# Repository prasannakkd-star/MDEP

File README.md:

# MDEP - Modular Distributed Embedded Platform

## Overview

MDEP is a modular embedded electronics platform built around a central motherboard and interchangeable peripheral modules.

## Hardware Modules

- Mainboard (prasanna) - central platform

- Audio Hub - audio-related module

- Motor Driver Hub - motor-control interface

- Sensor Hub - sensor interface

## Tools

- KiCad - schematic capture and PCB design

- Git - local version control

- GitHub - planned remote repository

## Development Status

- [x] Initial schematics and PCB layouts committed locally

- [ ] Assemble and test hardware

## Goals

- Reusable modular hardware

- Clear interfaces between modules

- Easier prototyping, debugging, and future expansion

## Notes

Hardware features and validation status will be updated as development progresses.

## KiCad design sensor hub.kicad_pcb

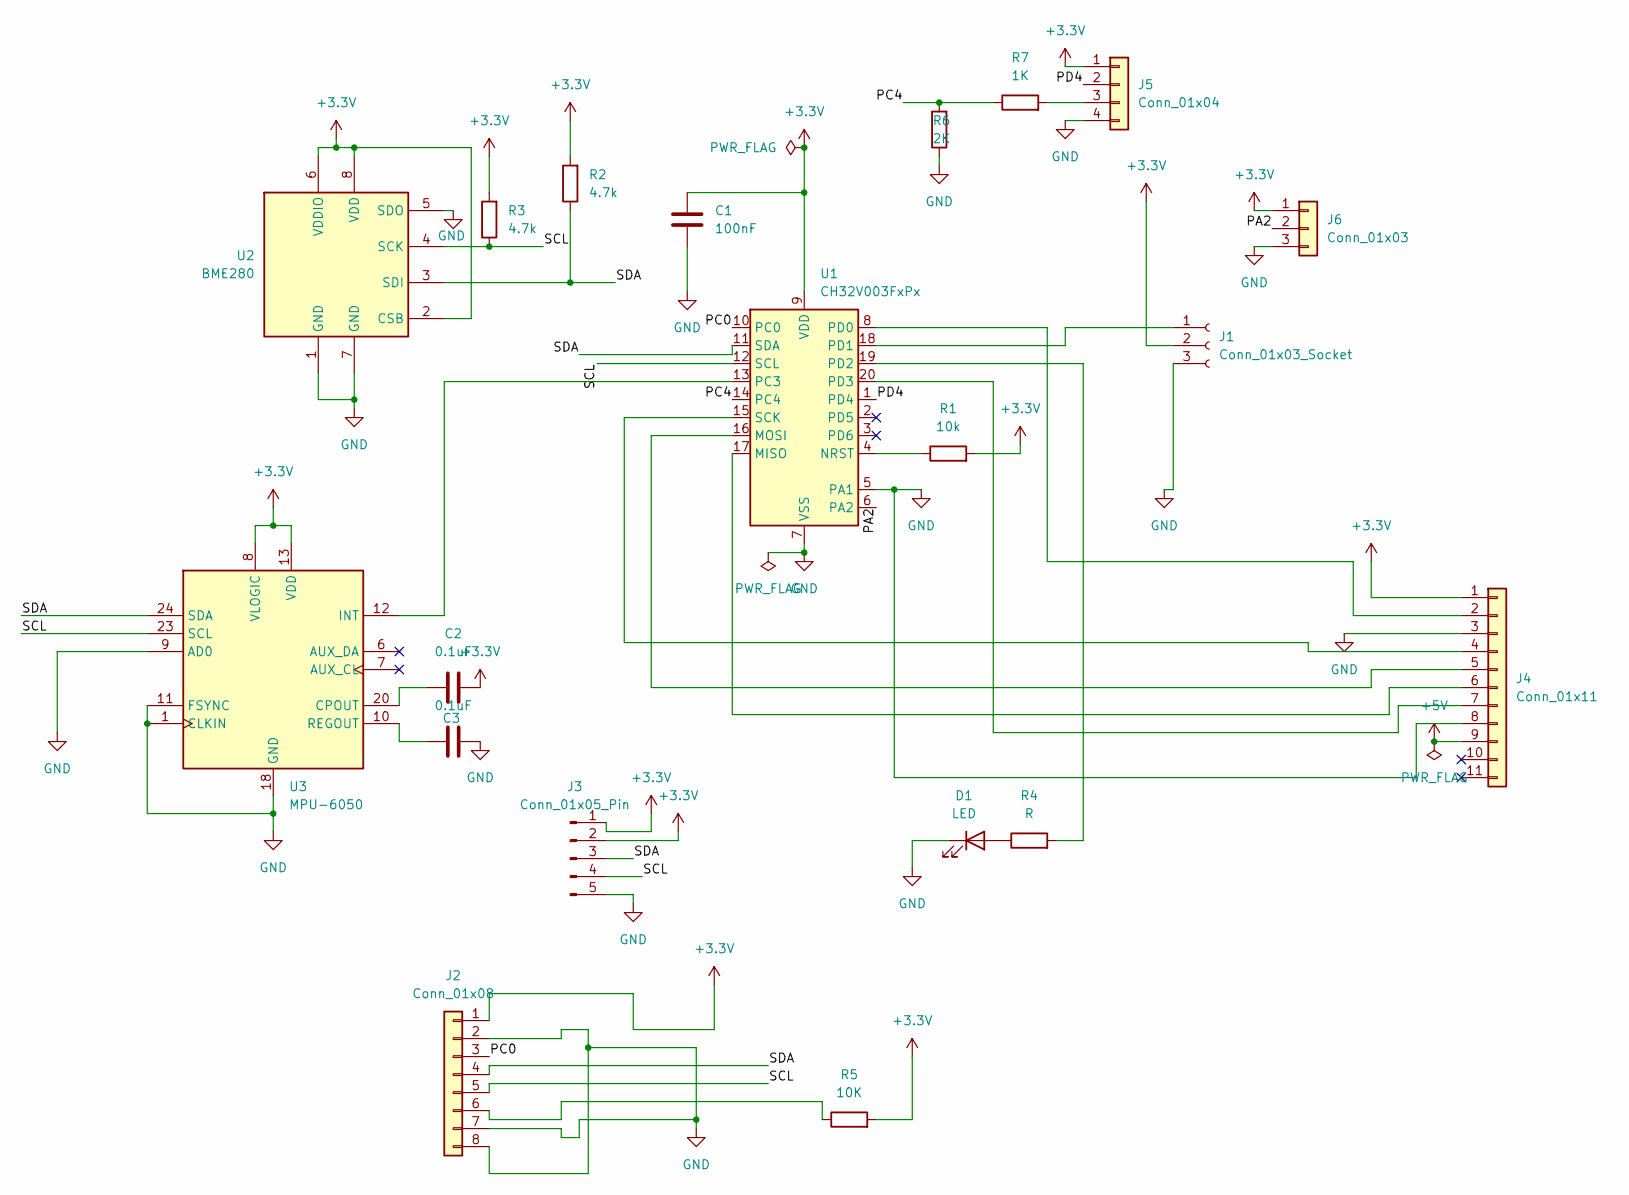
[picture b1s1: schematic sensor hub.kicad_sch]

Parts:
C1: 100nF; C_Disc_D3.0mm_W2.0mm_P2.50mm
C2, C3: 0.1uF
D1: LED; LED_D3.0mm
J1: Conn_01x03_Socket; PinHeader_1x03_P2.54mm_Vertical
J2: Conn_01x08; PinHeader_1x08_P2.54mm_Vertical
J3: Conn_01x05_Pin; PinHeader_1x05_P2.54mm_Vertical
J4: Conn_01x11; PinHeader_1x11_P2.54mm_Vertical
J5: Conn_01x04; PinHeader_1x04_P2.54mm_Vertical
J6: Conn_01x03; PinHeader_1x03_P2.54mm_Vertical
R1: 10k; R_Axial_DIN0207_L6.3mm_D2.5mm_P10.16mm_Horizontal
R2, R3: 4.7k; R_Axial_DIN0207_L6.3mm_D2.5mm_P10.16mm_Horizontal
R4: R; R_Axial_DIN0207_L6.3mm_D2.5mm_P10.16mm_Horizontal
R5: 10K; R_Axial_DIN0207_L6.3mm_D2.5mm_P10.16mm_Horizontal
R6: 2K; R_Axial_DIN0207_L6.3mm_D2.5mm_P10.16mm_Horizontal
R7: 1K; R_Axial_DIN0207_L6.3mm_D2.5mm_P10.16mm_Horizontal
U1: CH32V003FxPx; TSSOP-20_4.4x6.5mm_P0.65mm
U2: BME280; Bosch_LGA-8_2.5x2.5mm_P0.65mm_ClockwisePinNumbering
U3: MPU-6050; InvenSense_QFN-24_4x4mm_P0.5mm

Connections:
+3.3V: C1.1, C2.2, J1.2, J2.1, J3.1, J3.2, J4.1, J5.1, J6.1, R1.2, R2.2, R3.2, R5.2, U1.9 (VDD), U2.2 (CSB), U2.6 (VDDIO), U2.8 (VDD), U3.8 (VLOGIC), U3.13 (VDD)
+5V: J4.9
/PA2: J6.2, U1.6 (PA2)
/PC0: J2.3, U1.10 (PC0)
/PC4: R6.2, R7.1, U1.14 (PC4)
/PD4: J5.2, U1.1 (PD4)
/SCL: J2.5, J3.4, R3.1, U1.12 (SCL), U2.4 (SCK), U3.23 (SCL)
/SDA: J2.4, J3.3, R2.1, U1.11 (SDA), U2.3 (SDI), U3.24 (SDA)
GND: C1.2, C3.2, D1.1 (K), J1.3, J2.2, J2.7, J2.8, J3.5, J4.3, J4.8, J5.4, J6.3, R6.1, U1.5 (PA1), U1.7 (VSS), U2.1 (GND), U2.5 (SDO), U2.7 (GND), U3.1 (CLKIN), U3.9 (AD0), U3.11 (FSYNC), U3.18 (GND)
unnamed: D1.2 (A), R4.1
unnamed: J1.1, U1.18 (PD1)
unnamed: J2.6, R5.1
unnamed: J4.2, U1.8 (PD0)
unnamed: J4.4, U1.15 (SCK)
unnamed: J4.5, U1.16 (MOSI)
unnamed: J4.6, U1.17 (MISO)
unnamed: J4.7, U1.20 (PD3)
unnamed: J5.3, R7.2
unnamed: U1.13 (PC3), U3.12 (INT)
unnamed: R4.2, U1.19 (PD2)
unnamed: R1.1, U1.4 (NRST)
unnamed: C2.1, U3.20 (CPOUT)
unnamed: C3.1, U3.10 (REGOUT)

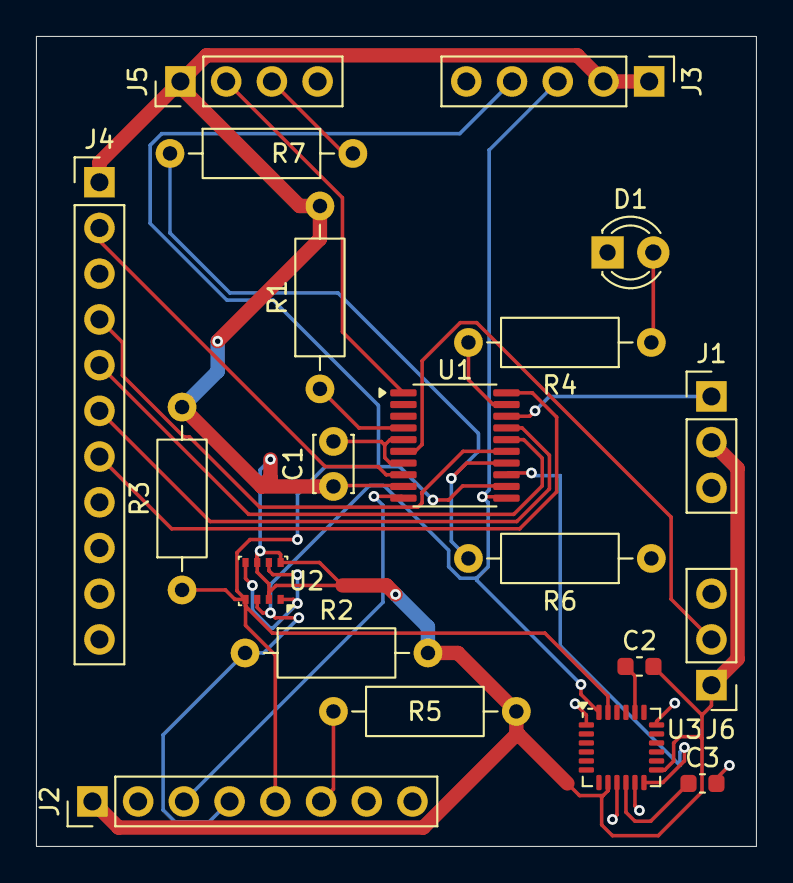
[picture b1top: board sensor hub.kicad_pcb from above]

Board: 2 copper layers, 40.0 x 45.0 mm, 20 parts (0 on the bottom side), 22 nets.

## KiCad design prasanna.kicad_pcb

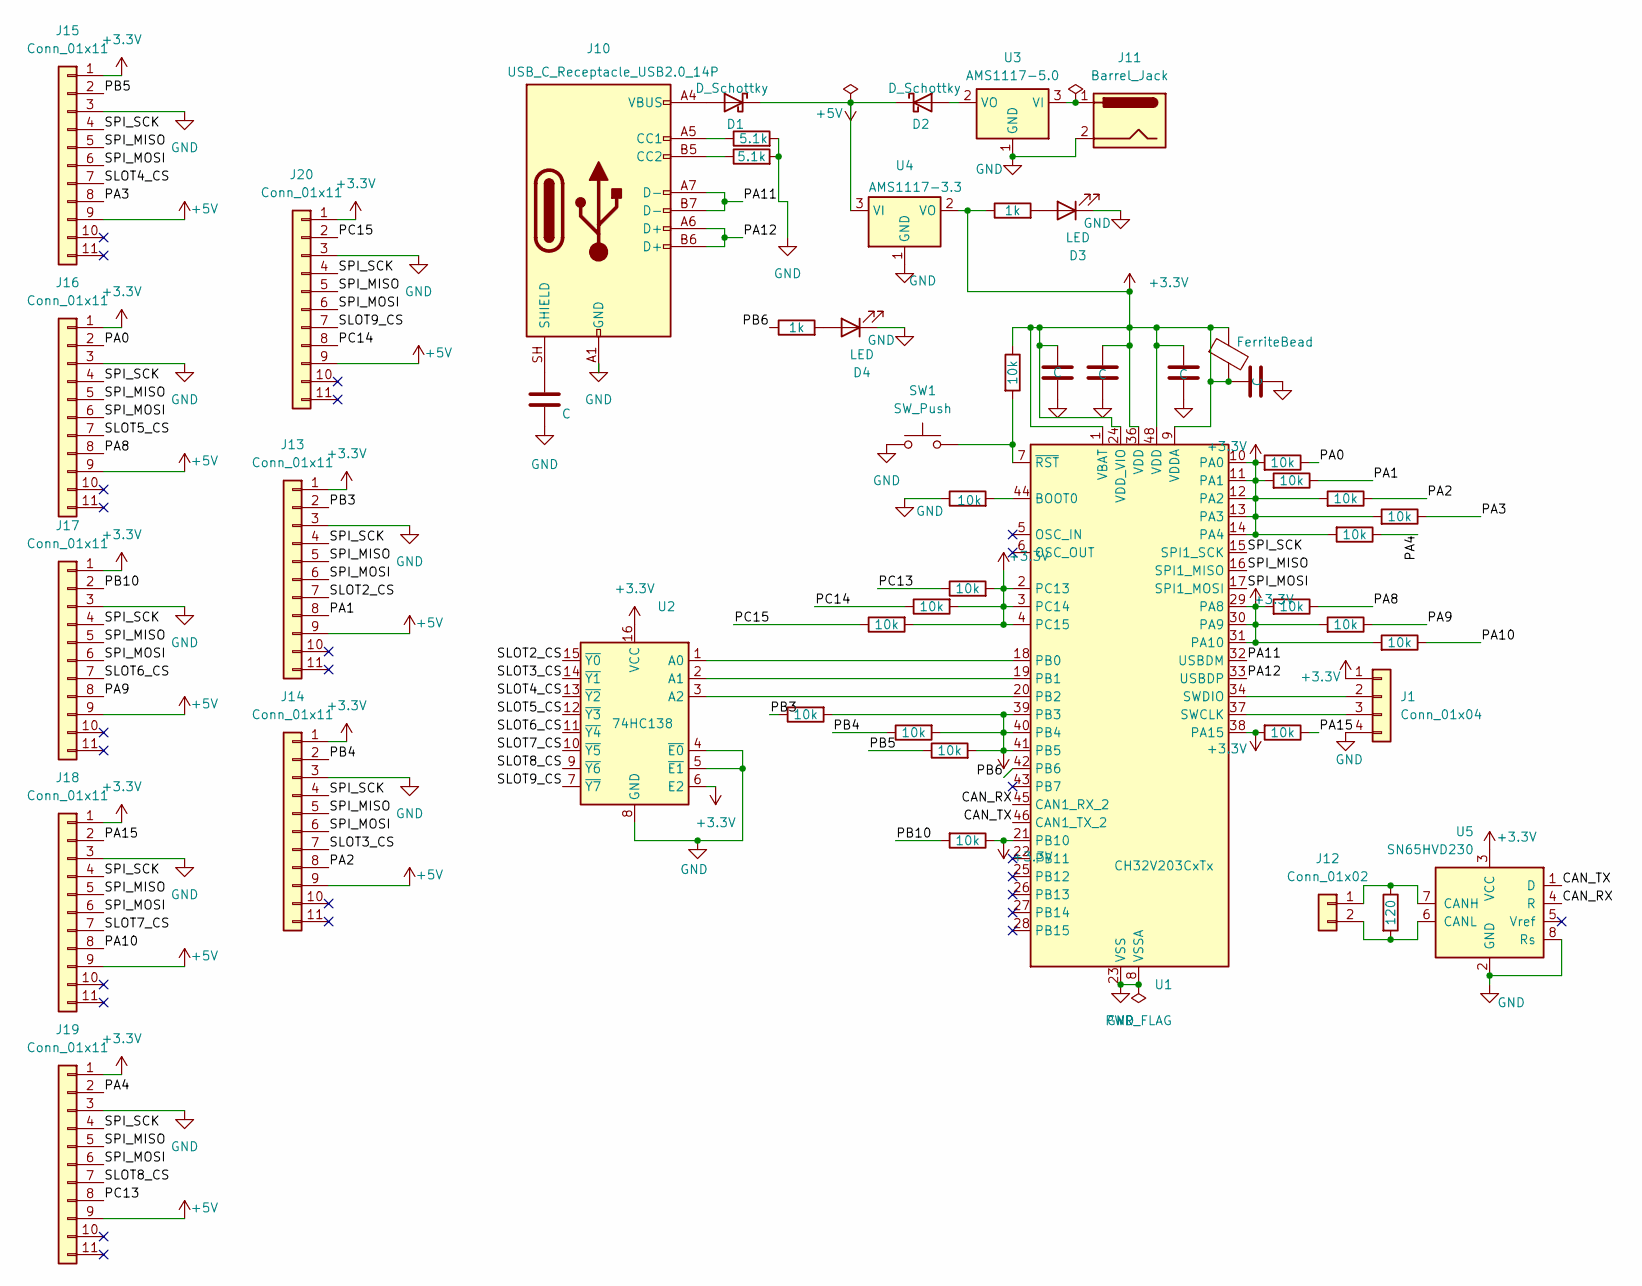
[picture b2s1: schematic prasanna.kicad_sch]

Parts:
C5, C6, C7, C8, C9: C; C_Disc_D3.0mm_W2.0mm_P2.50mm
D1, D2: D_Schottky; D_DO-41_SOD81_P10.16mm_Horizontal
D3, D4: LED; LED_D3.0mm
FB1: FerriteBead; L_0805_2012Metric
J1: Conn_01x04; PinHeader_1x04_P2.54mm_Vertical
J10: USB_C_Receptacle_USB2.0_14P; USB_C_Receptacle_GCT_USB4085
J11: Barrel_Jack; BarrelJack_Horizontal
J12: Conn_01x02; PinHeader_1x02_P2.54mm_Vertical
J13, J14, J15, J16, J17, J18, J19, J20: Conn_01x11; PinHeader_1x11_P2.54mm_Vertical
R1, R2, R3, R4, R5, R6, R7, R8, R9, R10, R13, R14, R15, R18, R19, R20, R21, R22: 10k; R_Axial_DIN0207_L6.3mm_D2.5mm_P10.16mm_Horizontal
R11, R12: 5.1k; R_Axial_DIN0207_L6.3mm_D2.5mm_P10.16mm_Horizontal
R23: 120; R_Axial_DIN0207_L6.3mm_D2.5mm_P10.16mm_Horizontal
R24, R25: 1k; R_Axial_DIN0207_L6.3mm_D2.5mm_P10.16mm_Horizontal
SW1: SW_Push; SW_PUSH_6mm
U1: CH32V203CxTx; LQFP-48_7x7mm_P0.5mm
U2: 74HC138; DIP-16_W7.62mm_Socket
U3: AMS1117-5.0; SOT-223-3_TabPin2
U4: AMS1117-3.3; SOT-223-3_TabPin2
U5: SN65HVD230; SOIC-8_3.9x4.9mm_P1.27mm

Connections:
+3.3V: C6.2, C7.2, C8.2, C9.2, FB1.1, FB1.2, J1.1, J13.1, J14.1, J15.1, J16.1, J17.1, J18.1, J19.1, J20.1, R1.1, R3.2, R4.2, R5.2, R6.2, R7.2, R8.2, R9.2, R10.2, R13.2, R14.2, R15.2, R18.2, R19.2, R20.2, R21.2, R22.1, R24.1, U1.1 (VBAT), U1.2 (PC13), U1.3 (PC14), U1.4 (PC15), U1.9 (VDDA), U1.10 (PA0), U1.11 (PA1), U1.12 (PA2), U1.13 (PA3), U1.14 (PA4), U1.21 (PB10), U1.24 (VDD_VIO), U1.29 (PA8), U1.30 (PA9), U1.31 (PA10), U1.36 (VDD), U1.38 (PA15), U1.39 (PB3), U1.40 (PB4), U1.41 (PB5), U1.48 (VDD), U2.6 (E2), U2.16 (VCC), U4.2 (VO), U5.3 (VCC)
+5V: D1.1 (K), D2.1 (K), J13.9, J14.9, J15.9, J16.9, J17.9, J18.9, J19.9, J20.9, U4.3 (VI)
/CAN_RX: U1.45 (CAN1_RX_2), U5.4 (R)
/CAN_TX: U1.46 (CAN1_TX_2), U5.1 (D)
/PA0: J16.2, R21.1
/PA1: J13.8, R3.1
/PA2: J14.8, R4.1
/PA3: J15.8, R5.1
/PA4: J19.2, R19.1
/PA8: J16.8, R6.1
/PA9: J17.8, R7.1
/PA10: J18.8, R8.1
/PA11: J10.A7 (D-), J10.B7 (D-), U1.32 (USBDM)
/PA12: J10.A6 (D+), J10.B6 (D+), U1.33 (USBDP)
/PA15: J18.2, R18.1
/PB3: J13.2, R13.1
/PB4: J14.2, R14.1
/PB5: J15.2, R15.1
/PB6: R25.1, U1.42 (PB6)
/PB10: J17.2, R22.2
/PC13: J19.8, R9.1
/PC14: J20.8, R10.1
/PC15: J20.2, R20.1
/SLOT2_CS: J13.7, U2.15 (~Y0)
/SLOT3_CS: J14.7, U2.14 (~Y1)
/SLOT4_CS: J15.7, U2.13 (~Y2)
/SLOT5_CS: J16.7, U2.12 (~Y3)
/SLOT6_CS: J17.7, U2.11 (~Y4)
/SLOT7_CS: J18.7, U2.10 (~Y5)
/SLOT8_CS: J19.7, U2.9 (~Y6)
/SLOT9_CS: J20.7, U2.7 (~Y7)
/SPI_MISO: J13.5, J14.5, J15.5, J16.5, J17.5, J18.5, J19.5, J20.5, U1.16 (SPI1_MISO)
/SPI_MOSI: J13.6, J14.6, J15.6, J16.6, J17.6, J18.6, J19.6, J20.6, U1.17 (SPI1_MOSI)
/SPI_SCK: J13.4, J14.4, J15.4, J16.4, J17.4, J18.4, J19.4, J20.4, U1.15 (SPI1_SCK)
GND: C5.2, C6.1, C7.1, C8.1, C9.1, D3.1 (K), D4.1 (K), J1.4, J10.A1 (GND), J10.A12 (GND), J10.B1 (GND), J10.B12 (GND), J11.2, J13.3, J14.3, J15.3, J16.3, J17.3, J18.3, J19.3, J20.3, R2.1, R11.2, R12.2, SW1.1, U1.8 (VSSA), U1.23 (VSS), U1.35 (VSS), U1.47 (VSS), U2.4 (~E0), U2.5 (~E1), U2.8 (GND), U3.1 (GND), U4.1 (GND), U5.2 (GND), U5.8 (Rs)
unnamed: D1.2 (A), J10.A4 (VBUS), J10.A9 (VBUS), J10.B4 (VBUS), J10.B9 (VBUS)
unnamed: D2.2 (A), U3.2 (VO)
unnamed: D3.2 (A), R24.2
unnamed: D4.2 (A), R25.2
unnamed: J1.2, U1.34 (SWDIO)
unnamed: J1.3, U1.37 (SWCLK)
unnamed: J10.A5 (CC1), R11.1
unnamed: J10.B5 (CC2), R12.1
unnamed: C5.1, J10.SH (SHIELD)
unnamed: J12.1, R23.1, U5.7 (CANH)
unnamed: J12.2, R23.2, U5.6 (CANL)
unnamed: R2.2, U1.44 (BOOT0)
unnamed: U1.18 (PB0), U2.1 (A0)
unnamed: U1.19 (PB1), U2.2 (A1)
unnamed: U1.20 (PB2), U2.3 (A2)
unnamed: R1.2, SW1.2, U1.7 (~RST)
unnamed: J11.1, U3.3 (VI)

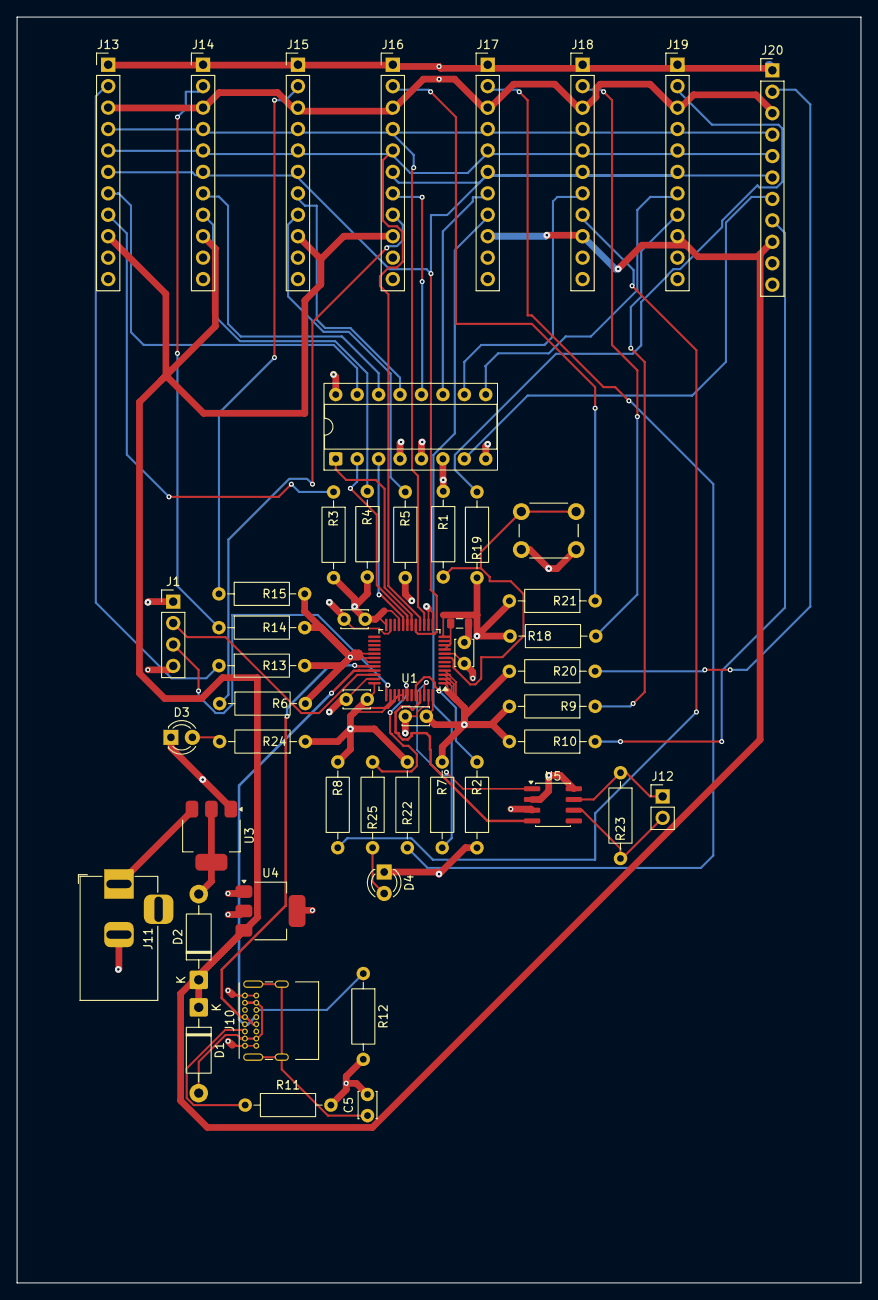
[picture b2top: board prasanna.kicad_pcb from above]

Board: 4 copper layers, 100.0 x 150.0 mm, 51 parts (0 on the bottom side), 52 nets.

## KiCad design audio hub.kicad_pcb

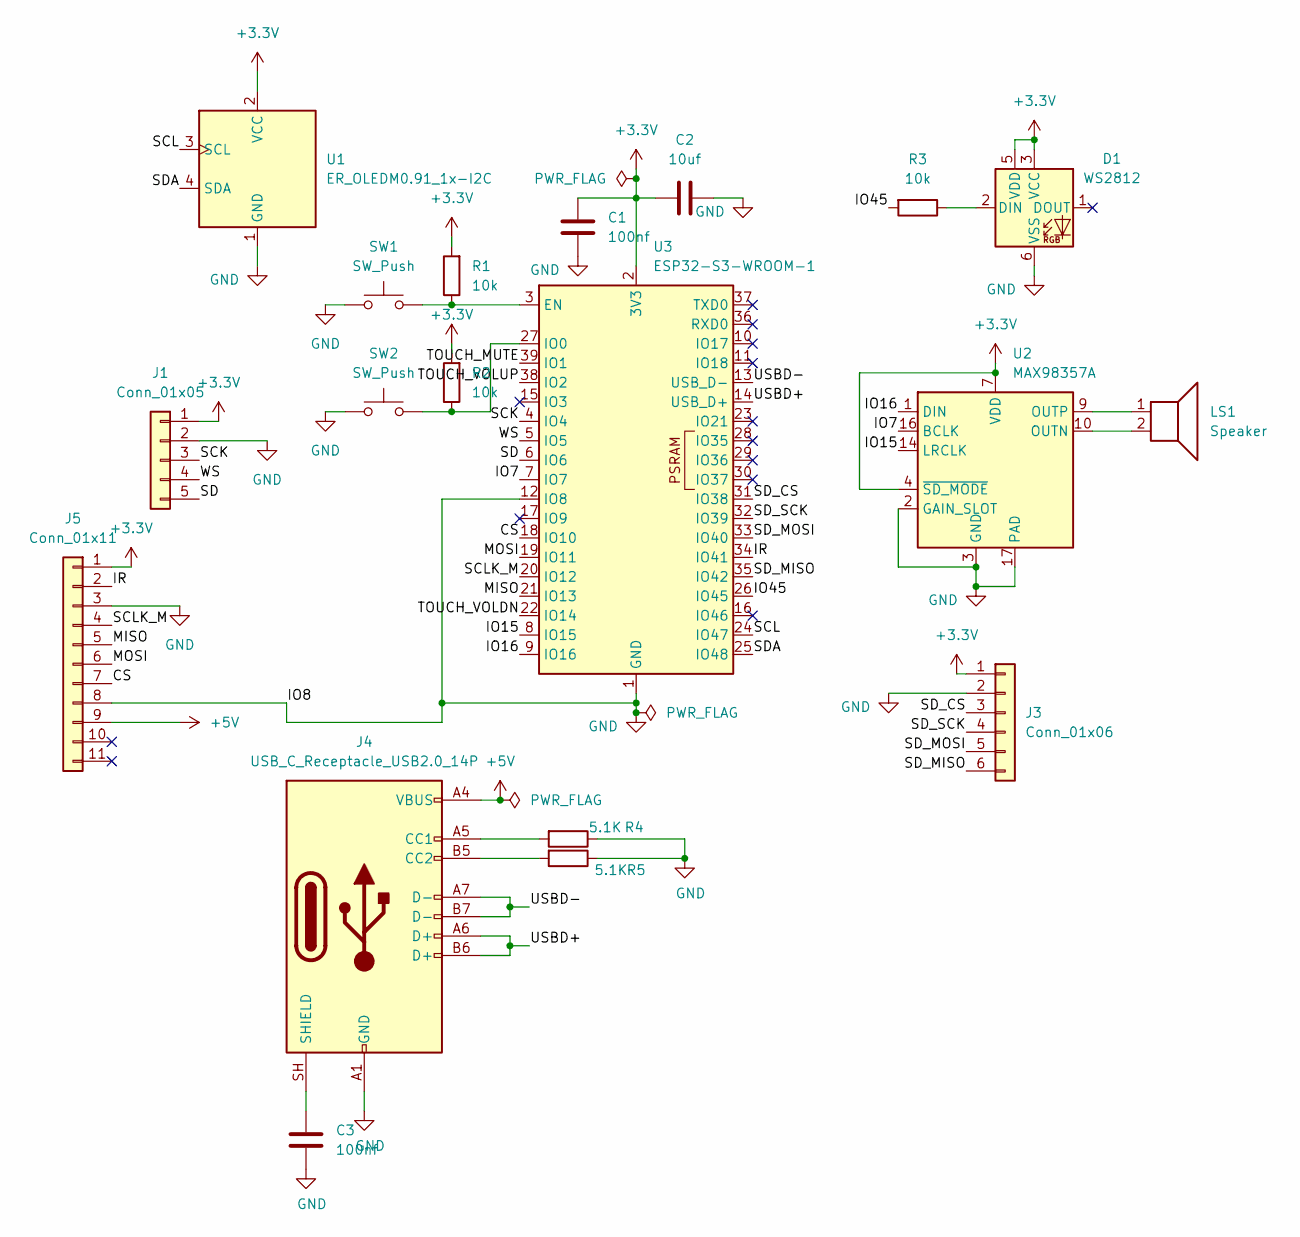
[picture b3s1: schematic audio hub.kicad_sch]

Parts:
C1, C3: 100nf; C_Disc_D3.0mm_W2.0mm_P2.50mm
C2: 10uf; CP_Radial_D5.0mm_P2.00mm
D1: WS2812; LED_WS2812_PLCC6_5.0x5.0mm_P1.6mm
J1: Conn_01x05; PinHeader_1x05_P2.54mm_Vertical
J3: Conn_01x06; PinHeader_1x06_P2.54mm_Vertical
J4: USB_C_Receptacle_USB2.0_14P; USB_C_Receptacle_GCT_USB4085
J5: Conn_01x11; PinHeader_1x11_P2.54mm_Vertical
LS1: Speaker
R1, R2, R3: 10k; R_Axial_DIN0207_L6.3mm_D2.5mm_P10.16mm_Horizontal
R4, R5: 5.1K; R_Axial_DIN0207_L6.3mm_D2.5mm_P10.16mm_Horizontal
SW1, SW2: SW_Push; SW_PUSH_6mm
U1: ER_OLEDM0.91_1x-I2C
U2: MAX98357A; TQFN-16-1EP_3x3mm_P0.5mm_EP1.23x1.23mm
U3: ESP32-S3-WROOM-1

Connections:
+3.3V: C1.1, C2.1, D1.3 (VCC), D1.5 (VDD), J1.1, J3.1, J5.1, R1.2, R2.2, U1.2 (VCC), U2.4 (~SD_MODE), U2.7 (VDD), U2.8 (VDD), U3.2 (3V3)
+5V: J4.A4 (VBUS), J4.A9 (VBUS), J4.B4 (VBUS), J4.B9 (VBUS), J5.9
/CS: J5.7, U3.18 (IO10)
/IO7: U2.16 (BCLK), U3.7 (IO7)
/IO15: U2.14 (LRCLK), U3.8 (IO15)
/IO16: U2.1 (DIN), U3.9 (IO16)
/IO45: R3.2, U3.26 (IO45)
/IR: J5.2, U3.34 (IO41)
/MISO: J5.5, U3.21 (IO13)
/MOSI: J5.6, U3.19 (IO11)
/SCK: J1.3, U3.4 (IO4)
/SCL: U1.3 (SCL), U3.24 (IO47)
/SCLK_M: J5.4, U3.20 (IO12)
/SD: J1.5, U3.6 (IO6)
/SDA: U1.4 (SDA), U3.25 (IO48)
/SD_CS: J3.3, U3.31 (IO38)
/SD_MISO: J3.6, U3.35 (IO42)
/SD_MOSI: J3.5, U3.33 (IO40)
/SD_SCK: J3.4, U3.32 (IO39)
/TOUCH_MUTE: U3.39 (IO1)
/TOUCH_VOLDN: U3.22 (IO14)
/TOUCH_VOLUP: U3.38 (IO2)
/USBD+: J4.A6 (D+), J4.B6 (D+), U3.14 (USB_D+)
/USBD-: J4.A7 (D-), J4.B7 (D-), U3.13 (USB_D-)
/WS: J1.4, U3.5 (IO5)
GND: C1.2, C2.2, C3.2, D1.6 (VSS), J1.2, J3.2, J4.A1 (GND), J4.A12 (GND), J4.B1 (GND), J4.B12 (GND), J5.3, J5.8, R4.1, R5.1, SW1.1, SW2.1, U1.1 (GND), U2.2 (GAIN_SLOT), U2.3 (GND), U2.11 (GND), U2.15 (GND), U2.17 (PAD), U3.1 (GND), U3.12 (IO8), U3.40 (GND), U3.41 (GND)
unnamed: D1.2 (DIN), R3.1
unnamed: J4.A5 (CC1), R4.2
unnamed: J4.B5 (CC2), R5.2
unnamed: C3.1, J4.SH (SHIELD)
unnamed: LS1.2, U2.10 (OUTN)
unnamed: LS1.1, U2.9 (OUTP)
unnamed: R1.1, SW1.2, U3.3 (EN)
unnamed: R2.1, SW2.2, U3.27 (IO0)

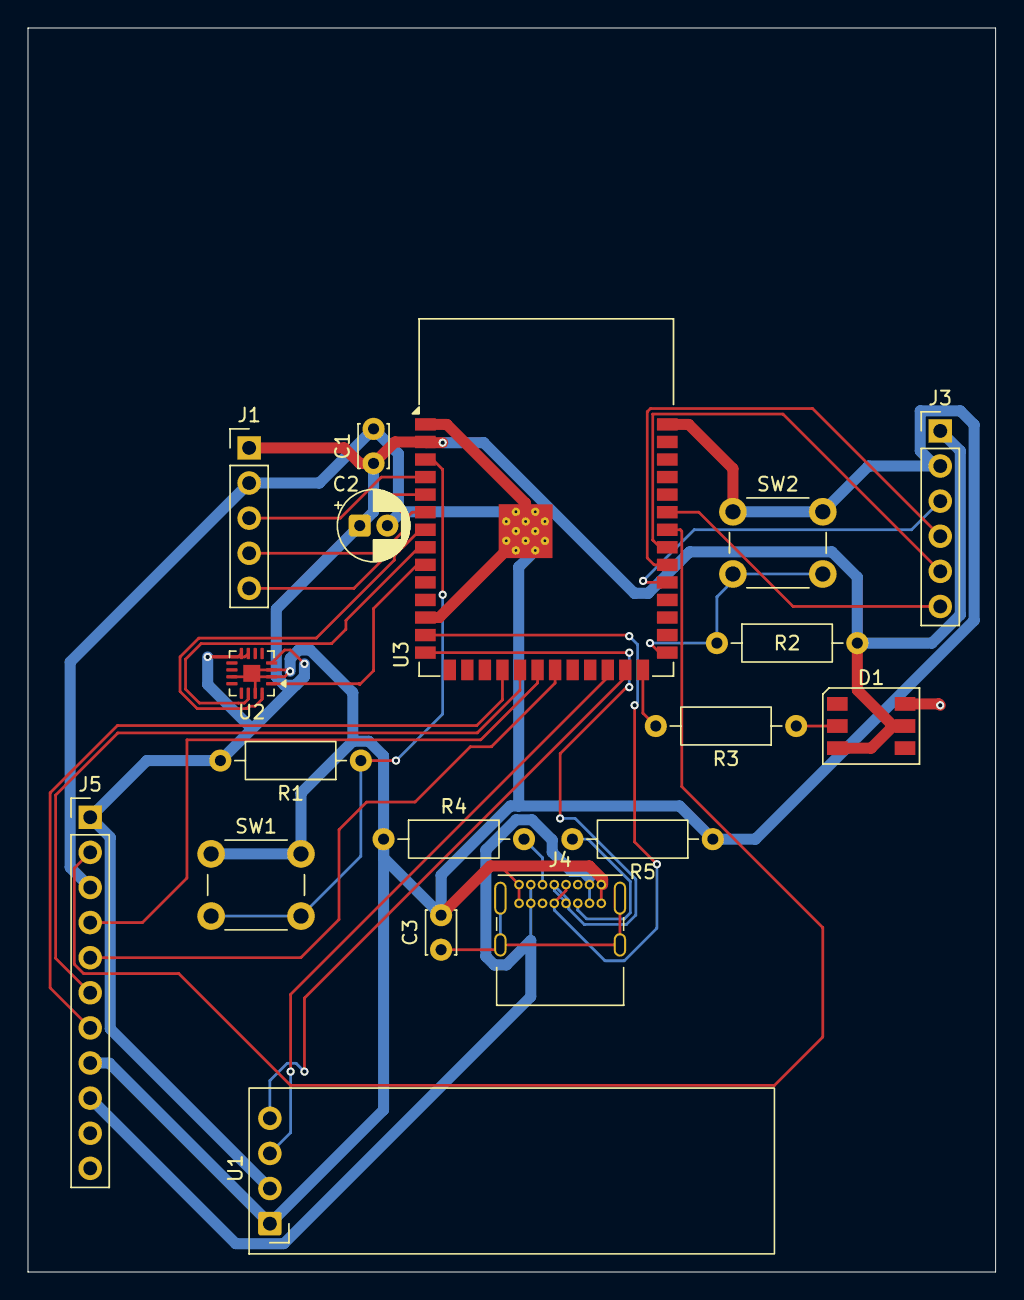
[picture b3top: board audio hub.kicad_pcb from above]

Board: 2 copper layers, 70.0 x 90.0 mm, 18 parts (0 on the bottom side), 29 nets.

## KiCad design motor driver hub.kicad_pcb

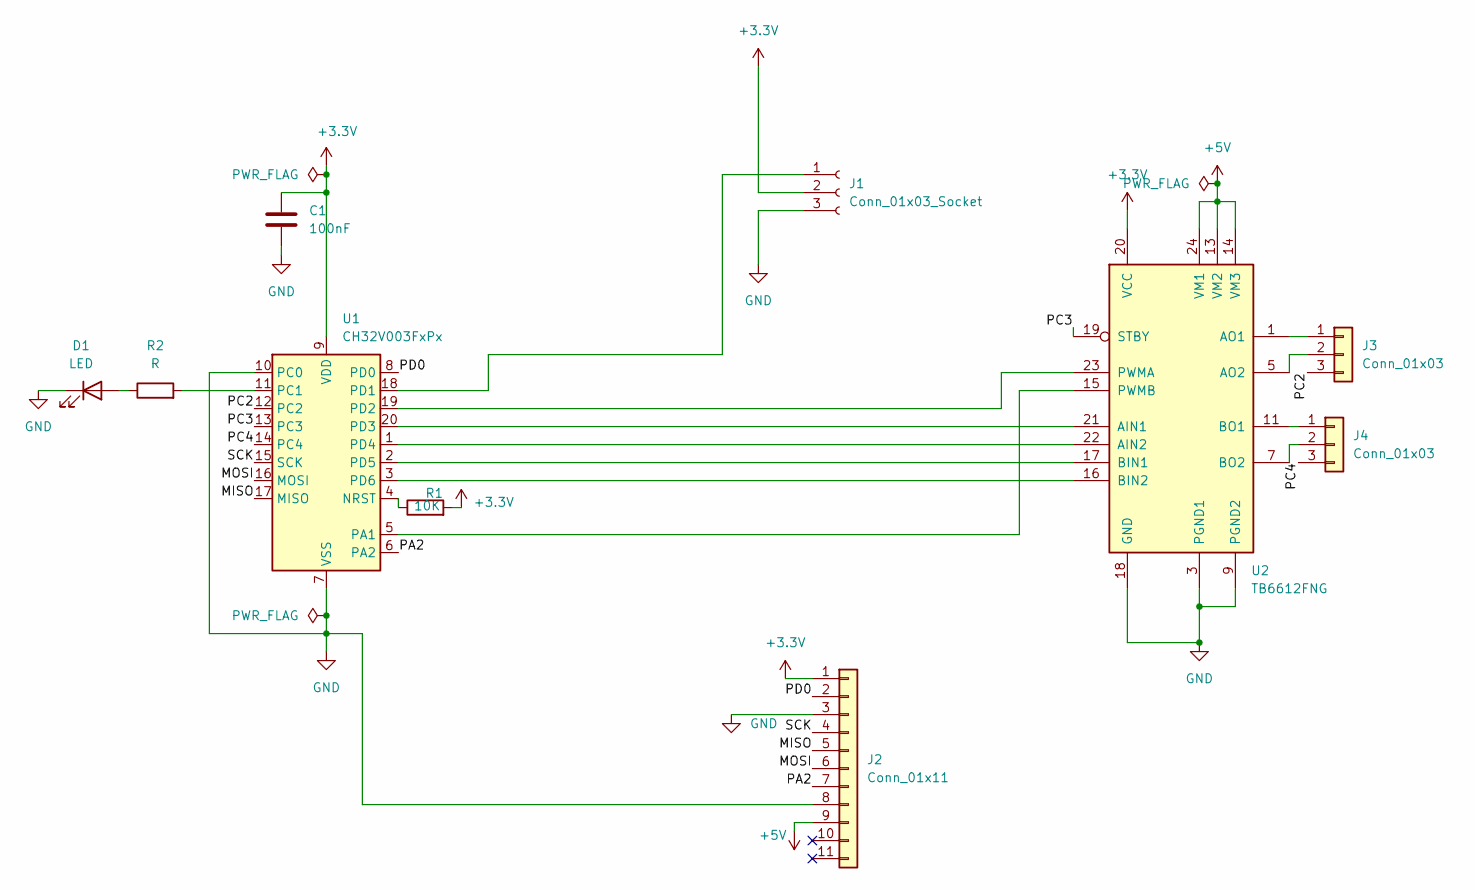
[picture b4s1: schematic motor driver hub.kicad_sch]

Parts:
C1: 100nF; C_Disc_D3.0mm_W2.0mm_P2.50mm
D1: LED; LED_D3.0mm
J1: Conn_01x03_Socket; PinHeader_1x03_P2.54mm_Vertical
J2: Conn_01x11; PinHeader_1x11_P2.54mm_Vertical
J3, J4: Conn_01x03; PinHeader_1x03_P2.54mm_Vertical
R1: 10K; R_Axial_DIN0207_L6.3mm_D2.5mm_P10.16mm_Horizontal
R2: R; R_Axial_DIN0207_L6.3mm_D2.5mm_P10.16mm_Horizontal
U1: CH32V003FxPx; TSSOP-20_4.4x6.5mm_P0.65mm
U2: TB6612FNG; SSOP-24_5.3x8.2mm_P0.65mm

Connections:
+3.3V: C1.1, J1.2, J2.1, R1.2, U1.9 (VDD), U2.20 (VCC)
+5V: J2.9, U2.13 (VM2), U2.14 (VM3), U2.24 (VM1)
/MISO: J2.5, U1.17 (MISO)
/MOSI: J2.6, U1.16 (MOSI)
/PA2: J2.7, U1.6 (PA2)
/PC2: J3.3, U1.12 (PC2)
/PC3: U1.13 (PC3), U2.19 (STBY)
/PC4: J4.3, U1.14 (PC4)
/PD0: J2.2, U1.8 (PD0)
/SCK: J2.4, U1.15 (SCK)
GND: C1.2, D1.1 (K), J1.3, J2.3, J2.8, U1.7 (VSS), U1.10 (PC0), U2.3 (PGND1), U2.4 (PGND1), U2.9 (PGND2), U2.10 (PGND2), U2.18 (GND)
unnamed: D1.2 (A), R2.1
unnamed: J1.1, U1.18 (PD1)
unnamed: J3.1, U2.1 (AO1), U2.2 (AO1)
unnamed: J3.2, U2.5 (AO2), U2.6 (AO2)
unnamed: J4.1, U2.11 (BO1), U2.12 (BO1)
unnamed: J4.2, U2.7 (BO2), U2.8 (BO2)
unnamed: U1.5 (PA1), U2.15 (PWMB)
unnamed: R2.2, U1.11 (PC1)
unnamed: U1.19 (PD2), U2.23 (PWMA)
unnamed: U1.20 (PD3), U2.21 (AIN1)
unnamed: U1.1 (PD4), U2.22 (AIN2)
unnamed: U1.2 (PD5), U2.17 (BIN1)
unnamed: U1.3 (PD6), U2.16 (BIN2)
unnamed: R1.1, U1.4 (NRST)

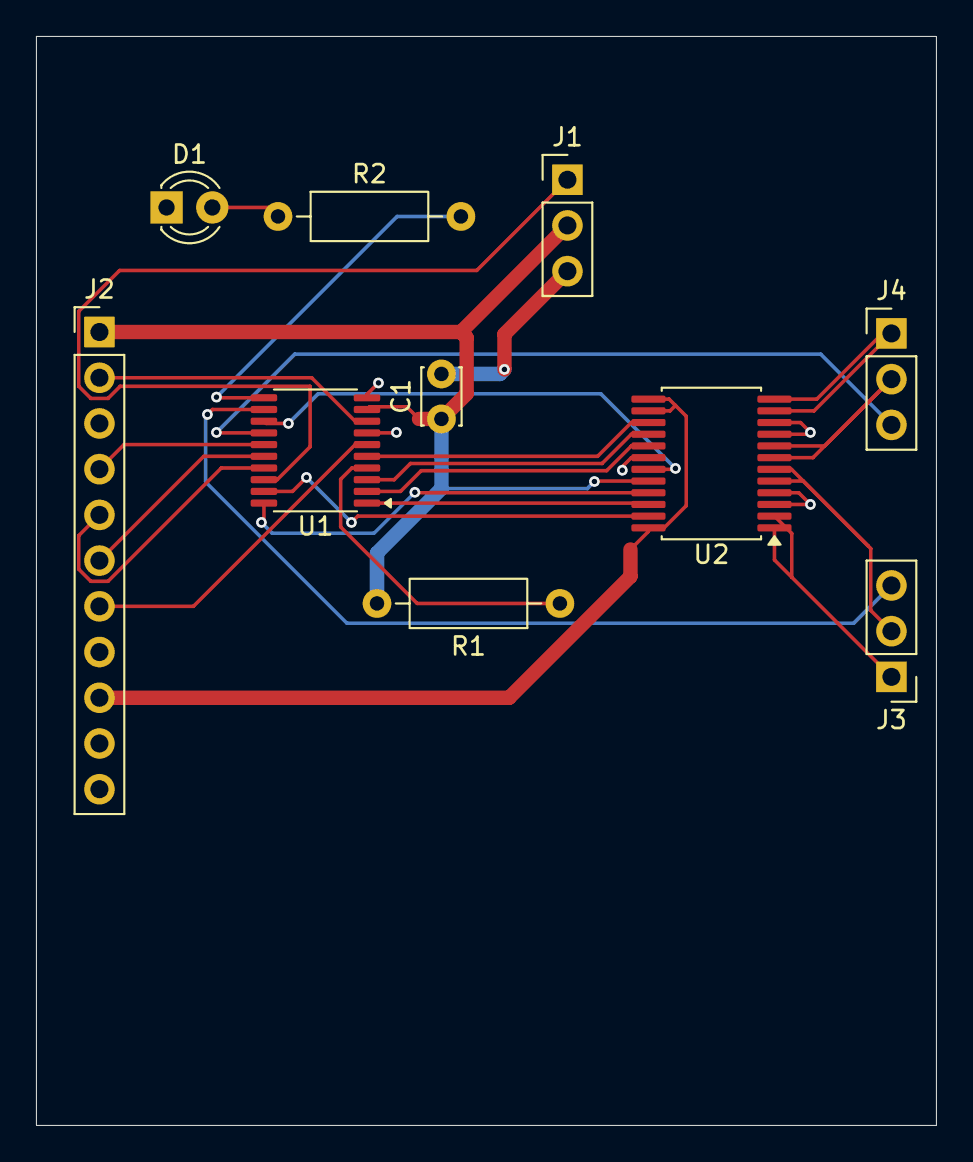
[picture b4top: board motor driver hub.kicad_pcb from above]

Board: 2 copper layers, 50.0 x 60.5 mm, 10 parts (0 on the bottom side), 25 nets.
